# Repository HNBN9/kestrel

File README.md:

# Kestrel

Kestrel is a wireless Bluetooth split keyboard with a distinctive layout: a 3×5 − 2 main layout on both the left and right halves, each with two vertically arranged thumb keys.

The right half has a 19 mm trackball using the PMW3610 sensor, and the left half mirrors it with a 5-way switch. In total the keyboard has 32 + 5 keys (the 5 being the inputs of the 5-way switch).

It is designed with portability and usability in mind.

> > **Warning — Right Half Power Management**
>
> The current revision has a critical flaw in the right-side power management circuit. The LiPo charging and power delivery circuitry may not function correctly, potentially resulting in battery over-discharge and permanent damage.
>
> **If you still wish to use this revision**, remove all components belonging to the right-side boost converter circuit before connecting the LiPo battery directly to the XIAO's BAT+ and GND pads. Ensure that the battery charging and protection circuitry remains properly connected and functional.
>
> This workaround is provided as-is and has not been validated as a reliable fix. Use at your own risk.
>
> A redesigned power management circuit is planned for V2.

## Features

- Wireless Bluetooth split keyboard running ZMK
- 3×5 − 2 main layout with two vertical thumb keys per half
- 19 mm trackball (PMW3610) on the right half
- 5-way switch on the left half
- 3D-printed integrated hinge that bends close to 90° and provides built-in tenting
- Charlieplex matrix on the right half, with a dedicated 3V3 DC/DC converter circuit

## Specifications

| Item | Description |
|---|---|
| Form Factor | Split, wireless (Bluetooth) |
| Main Layout | 3×5 − 2, plus 2 vertical thumb keys per half |
| Keys | 32 + 5 (5-way switch) |
| Right Half | 19 mm trackball (PMW3610), charlieplex matrix, 3V3 DC/DC converter, central |
| Left Half | 5-way switch, standard key matrix, peripheral |
| Firmware | ZMK |
| Case | 3D-printed with integrated hinge |

## Hardware

### Hinge

The most distinctive feature of Kestrel is its 3D-printed hinge.

The built-in hinge bends close to 90° and supports tenting on its own. It keeps a suitable amount of torque for use on a keyboard.

### Left Half: 5-Way Switch

The left half uses a regular key matrix so that the 5-way switch can be included.

The 5-way switch supports a center click and pushing in four directions. However, it is prone to accidental inputs and its lifespan is not expected to be long. For this reason it is used for conservative functions such as arrow keys and switching between QWERTY and Colemak layers.

### Right Half: Trackball and Charlieplex Matrix

The right half uses a charlieplex matrix to work around the limited number of pins caused by the trackball. Because the trackball is on the right, the right half acts as the central and the left half as the peripheral.

Unlike col2row (or row2col) matrices, charlieplex pins have no fixed input and output roles, which makes it prone to ghosting. Charlieplex keyboards commonly deal with this by using the voltage drop across different numbers of diodes, so that a ghosted key falls outside the input range of the pin.

For this to work reliably, the supply voltage must stay constant. The right half therefore includes an additional 3V3 DC/DC converter circuit. Without it, ghosting increases sharply as the battery level drops.

> [!NOTE]
> The BOM for this design uses a WSON package for the 3V3 converter. If you do not order a PCBA, you will need to hand-solder the WSON package yourself. Modifying the circuit to use a similar-performance package that is easier to hand-solder is recommended.

### PCB

### Credits

- The charlieplex matrix is based on [Hooky's round-robin schematics](https://github.com/HookyKB/round-robin-schematics).
- The 3V3 circuit is based on [DYA Dash](https://github.com/cormoran/dya-dash-keyboard).
- The PMW3610 breakout board is a modified version of [ufan's pmw3610_breakout](https://github.com/ufan/pmw3610_breakout).

## Firmware

Kestrel runs on [ZMK Firmware](https://zmk.dev/).

The keyboard-specific configuration is maintained in a separate repository:

**[Kestrel ZMK Configuration](https://github.com/HNBN9/zmk-config-kestrel)**

The firmware files show how different matrices are applied to each half in ZMK. The matrix transform is shared between both halves, while the `kscan` configuration is written separately for the left and right halves.

## Gallery

## Known Issues

- The reverse-current blocking MOSFET in the right half's charging circuit has been reported to prevent proper charging. Remove the MOSFET and short its pads as a workaround (this removes the reverse-current protection).

## Repository Status

This repository currently contains the case STEP files and PCB-related files.

## License

This project uses separate licenses for software and non-software materials.

| Material | License |
|---|---|
| Firmware configuration and source code | [MIT License](./LICENSE-MIT) |
| Hardware design files (PCB, case), documentation, photographs, and renders | [CC BY-NC 4.0](./LICENSE-CC-BY-NC) |

Parts derived from other projects (see [Credits](#credits)) remain subject to the terms of their original authors.

ZMK Firmware itself is distributed under its own license; see the [ZMK repository](https://github.com/zmkfirmware/zmk).

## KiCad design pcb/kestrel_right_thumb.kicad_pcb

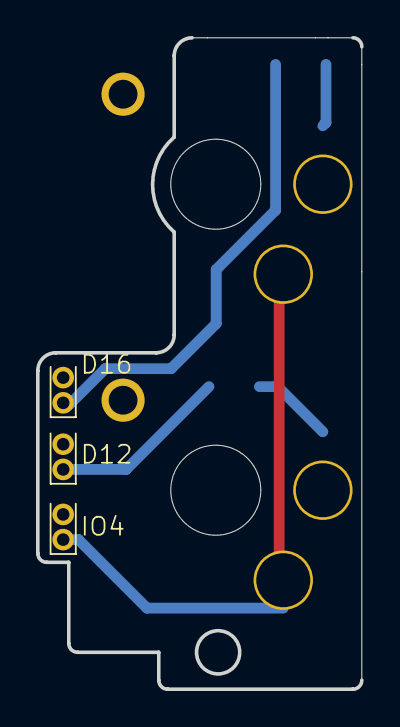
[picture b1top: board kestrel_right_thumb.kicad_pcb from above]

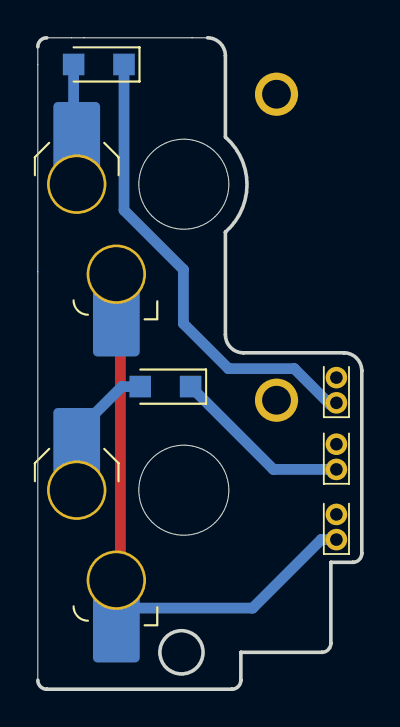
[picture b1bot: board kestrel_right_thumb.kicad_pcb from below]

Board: 2 copper layers, 18.0 x 36.2 mm, 4 parts (4 on the bottom side), 3 nets.

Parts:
D15, D16: 1N4148; Nexperia_CFP3_SOD-123W
RC4-3, RC4-4: SW_Push; SW_choc_v2_HS_CPG135001S30_1u

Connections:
IO 4: RC4-3.1, RC4-4.1
unnamed: D15.2 (A), RC4-3.2
unnamed: D16.2 (A), RC4-4.2

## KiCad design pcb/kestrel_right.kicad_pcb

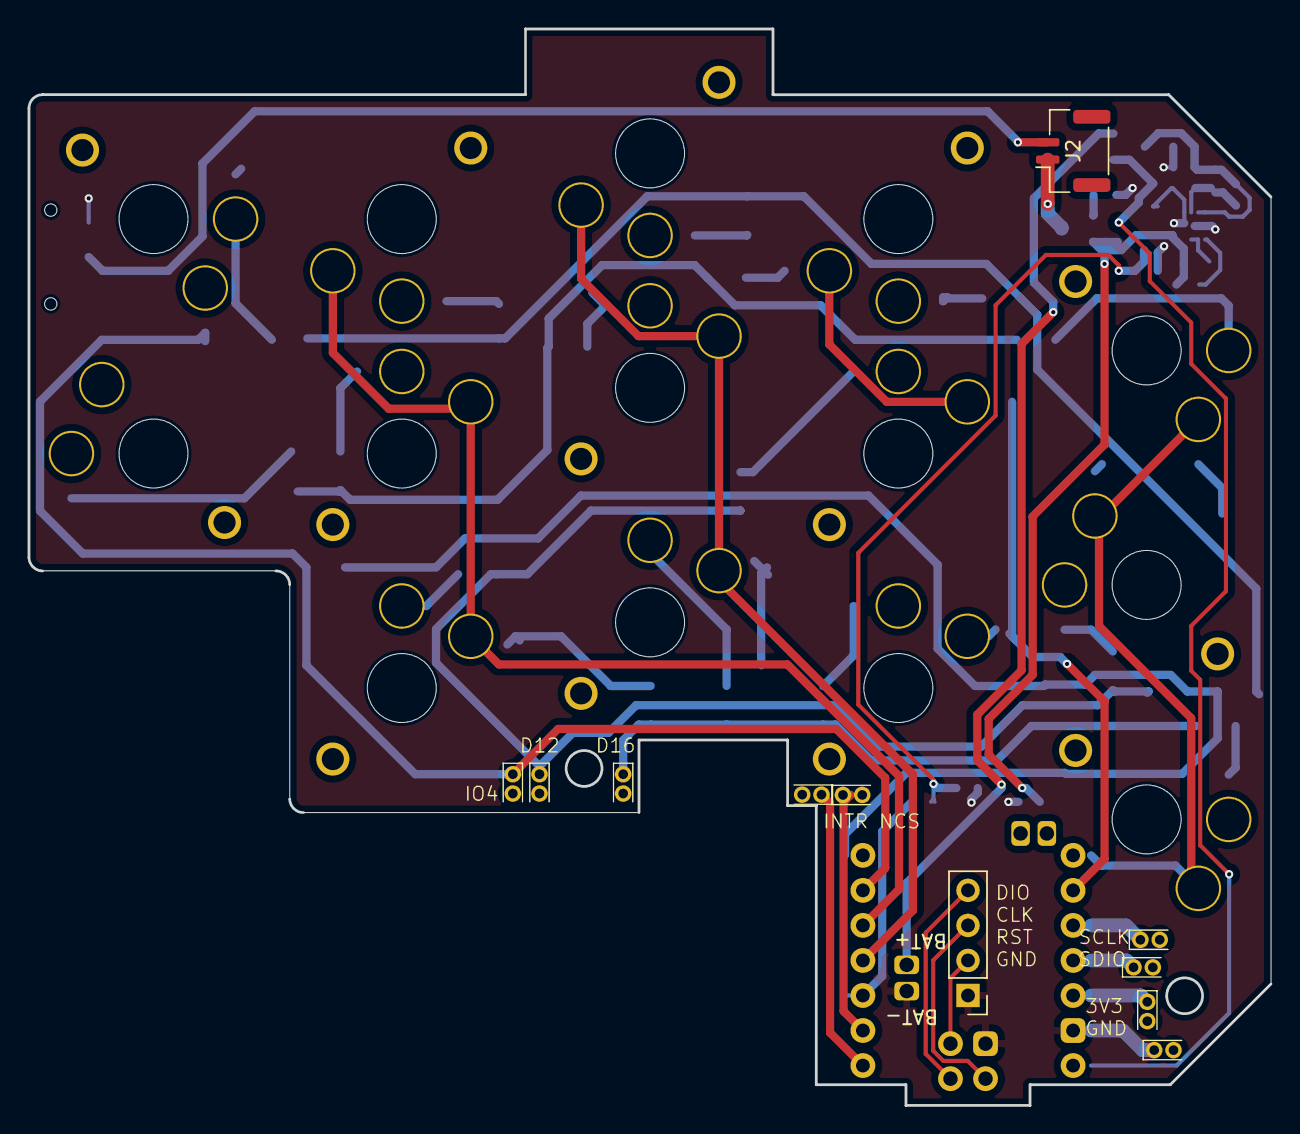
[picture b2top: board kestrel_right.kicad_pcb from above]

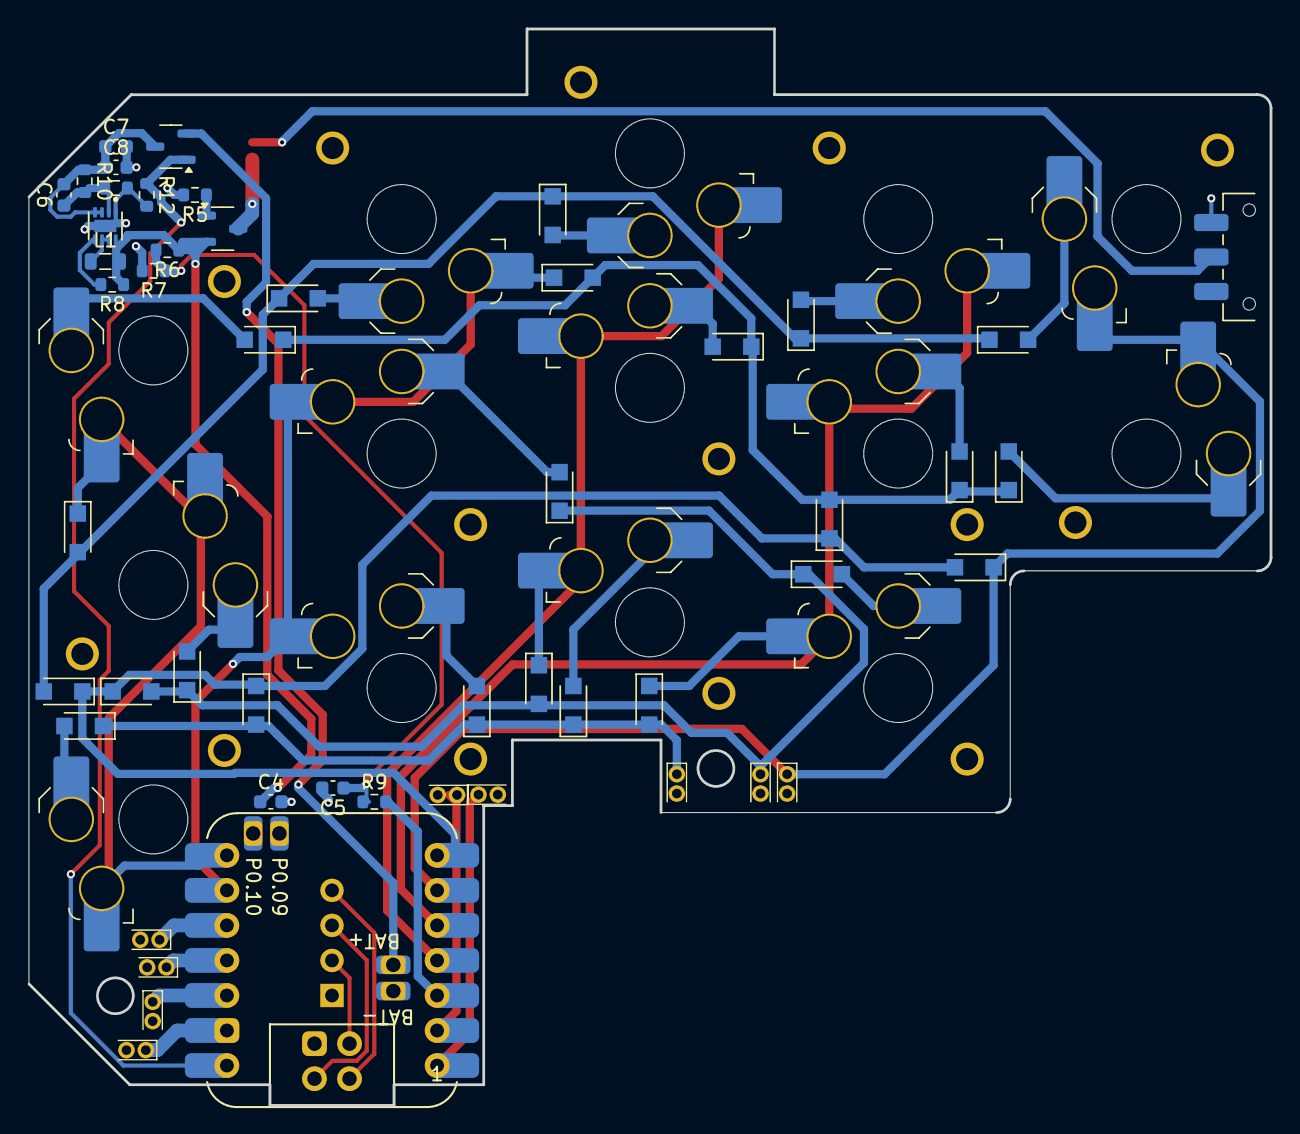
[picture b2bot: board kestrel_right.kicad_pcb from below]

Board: 2 copper layers, 90.0 x 78.0 mm, 57 parts (56 on the bottom side), 37 nets.

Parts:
C4: 10uF; C_0603_1608Metric
C5: 0.1uF; C_0603_1608Metric
C6: 20pf; C_0603_1608Metric
C7, C8: 10u; C_0603_1608Metric
D1, D2, D3, D4, D5, D6, D7, D8, D9, D10, D11, D12, D13, D14: 1N4148; Nexperia_CFP3_SOD-123W
DI1, DI2, DI3, DI4: 1N4148; Nexperia_CFP3_SOD-123W
DS1, DS2, DS3, DS4, DS5: 1N4148; Nexperia_CFP3_SOD-123W
J2: JST 1.25mm; JST_GH_SM02B-GHS-TB_1x02-1MP_P1.25mm_Horizontal
L1: 0.47uH; L_0805_2012Metric
Q2, Q3: AO3401A; SOT-23-3
R5, R8, R9, R12: 100k; R_0603_1608Metric
R6: 1M; R_0603_1608Metric
R7, R10: 470k; R_0603_1608Metric
R11: 150k; R_0603_1608Metric
RC0-1, RC0-2, RC0-3, RC1-1, RC1-2, RC1-3, RC2-1, RC2-2, RC2-3, RC3-1, RC3-2, RC3-3, RC4-1, RC4-2: SW_Push; SW_choc_v2_HS_CPG135001S30_1u
SW2: SW_SPDT; SW_SPDT_CK_JS102011SAQN
U2: TPS61021ADSGR
U3: Seeeduino Xiao nRF52840; Xiao_nRF52840_ACH

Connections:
BAT+: Q3.2 (S), U3.16 (BAT+)
GND: C4.2, C5.2, C7.2, C8.2, R5.2, R7.2, R11.2, R12.2, SW2.3 (C), U2.1 (AGND), U2.9 (PGND), U3.9 (GND), U3.15 (BAT-), U3.22 (GND)
INPUT_VOLTAGE: C5.1, R6.2, R7.1, R9.1
INTR: DI1.1 (K), DI2.1 (K), DI3.1 (K), DI4.1 (K), DS5.2 (A), U3.7 (P1.11)
IO 0: DS1.1 (K), RC0-1.1, RC0-2.1, RC0-3.1, U3.14 (P1.12)
IO 1: DS2.1 (K), RC1-1.1, RC1-2.1, RC1-3.1, U3.13 (P1.13)
IO 2: DS3.1 (K), RC2-1.1, RC2-2.1, RC2-3.1, U3.4 (P0.29)
IO 3: DS4.1 (K), RC3-1.1, RC3-2.1, RC3-3.1, U3.5 (P0.04)
IO 4: DS5.1 (K), RC4-1.1, RC4-2.1, U3.6 (P0.05)
unnamed: D1.2 (A), RC0-1.2
unnamed: D1.1 (K), D8.1 (K), D11.1 (K), D14.1 (K), DI2.2 (A), DS2.2 (A)
unnamed: D2.2 (A), RC0-2.2
unnamed: D3.2 (A), RC0-3.2
unnamed: D4.2 (A), RC1-1.2
unnamed: D5.2 (A), RC1-2.2
unnamed: D6.2 (A), RC1-3.2
unnamed: D7.2 (A), RC2-1.2
unnamed: D8.2 (A), RC2-2.2
unnamed: D9.2 (A), RC2-3.2
unnamed: D10.2 (A), RC3-1.2
unnamed: D4.1 (K), D7.1 (K), D10.1 (K), D13.1 (K), DI1.2 (A), DS1.2 (A)
unnamed: D11.2 (A), RC3-2.2
unnamed: D12.2 (A), RC3-3.2
unnamed: D2.1 (K), D5.1 (K), D12.1 (K), DI3.2 (A), DS3.2 (A)
unnamed: D13.2 (A), RC4-1.2
unnamed: D14.2 (A), RC4-2.2
unnamed: D3.1 (K), D6.1 (K), D9.1 (K), DI4.2 (A), DS4.2 (A)
unnamed: J2.1, Q2.3 (D)
unnamed: J2.2, SW2.2 (B)
unnamed: L1.1, U2.6 (SW), U2.7 (SW)
unnamed: Q2.1 (G), R5.1
unnamed: C4.1, L1.2, Q2.2 (S), R6.1, R8.1, U2.8 (VIN)
unnamed: C6.2, C7.1, C8.1, Q3.3 (D), R10.1, U2.3 (VOUT), U2.4 (VOUT)
unnamed: R8.2, U2.5 (EN)
unnamed: C6.1, R10.2, R11.1, U2.2 (FB)
unnamed: R9.2, U3.3 (P0.28)
VBUS: Q3.1 (G), R12.1, U3.8 (5V)

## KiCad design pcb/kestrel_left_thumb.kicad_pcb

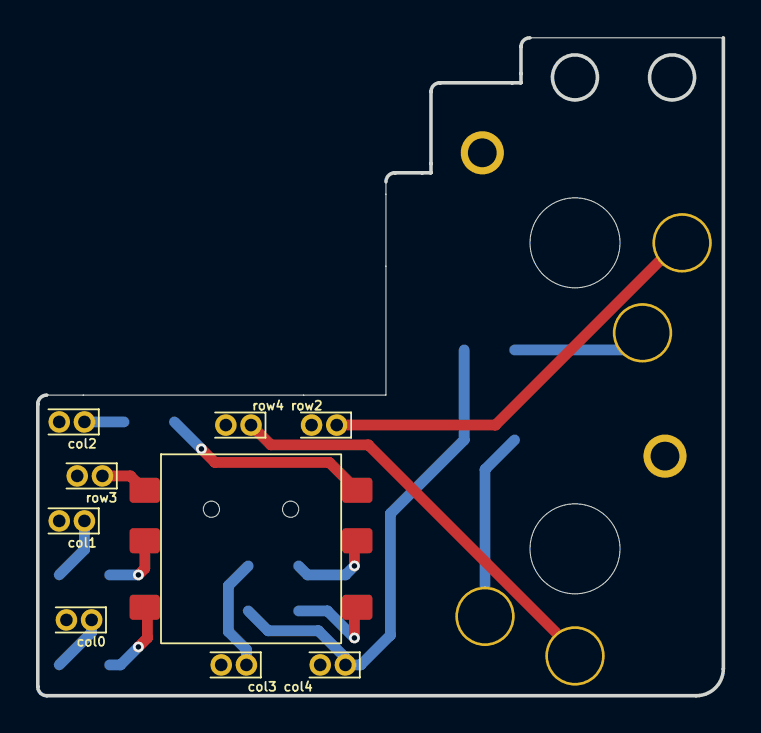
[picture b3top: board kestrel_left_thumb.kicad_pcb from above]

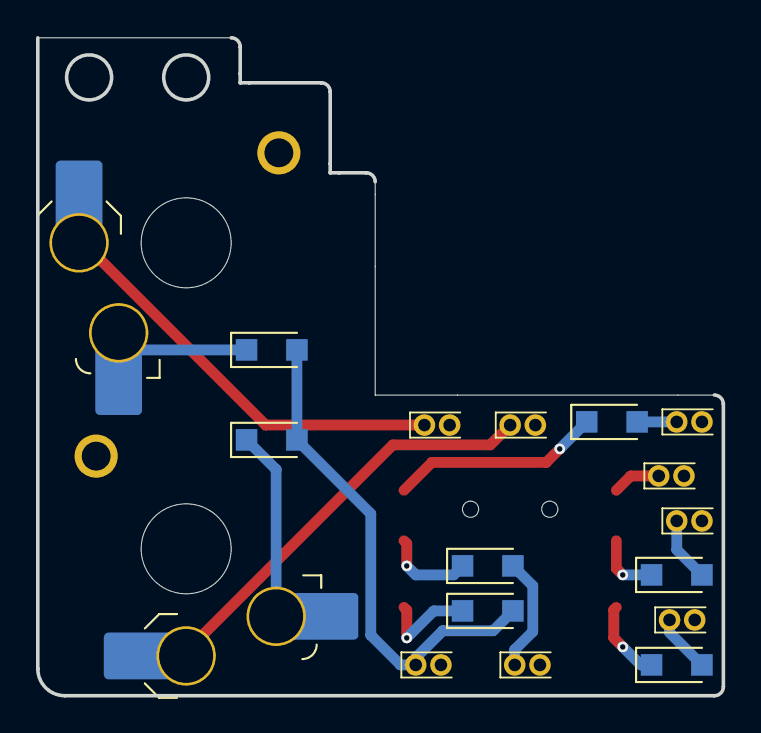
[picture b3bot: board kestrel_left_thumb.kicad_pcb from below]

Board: 2 copper layers, 38.1 x 36.5 mm, 10 parts (9 on the bottom side), 8 nets.

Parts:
5SW1: 5 way switch
DL1, DL5, DL9, DL13, DL17, DL20, DL21: 1N4148; Nexperia_CFP3_SOD-123W
LC15, LC16: SW_choc_v2_HS_CPG135001S30_1u

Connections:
unnamed: 5SW1.F2 (2), DL5.1 (K)
unnamed: 5SW1.F5 (3), DL1.1 (K)
unnamed: 5SW1.F1 (4), DL9.1 (K)
unnamed: 5SW1.F4 (5), DL13.1 (K)
unnamed: 5SW1.F3 (6), DL17.1 (K)
unnamed: DL20.1 (K), LC15.1
unnamed: DL21.1 (K), LC16.1
col4: DL17.2 (A), DL20.2 (A), DL21.2 (A)

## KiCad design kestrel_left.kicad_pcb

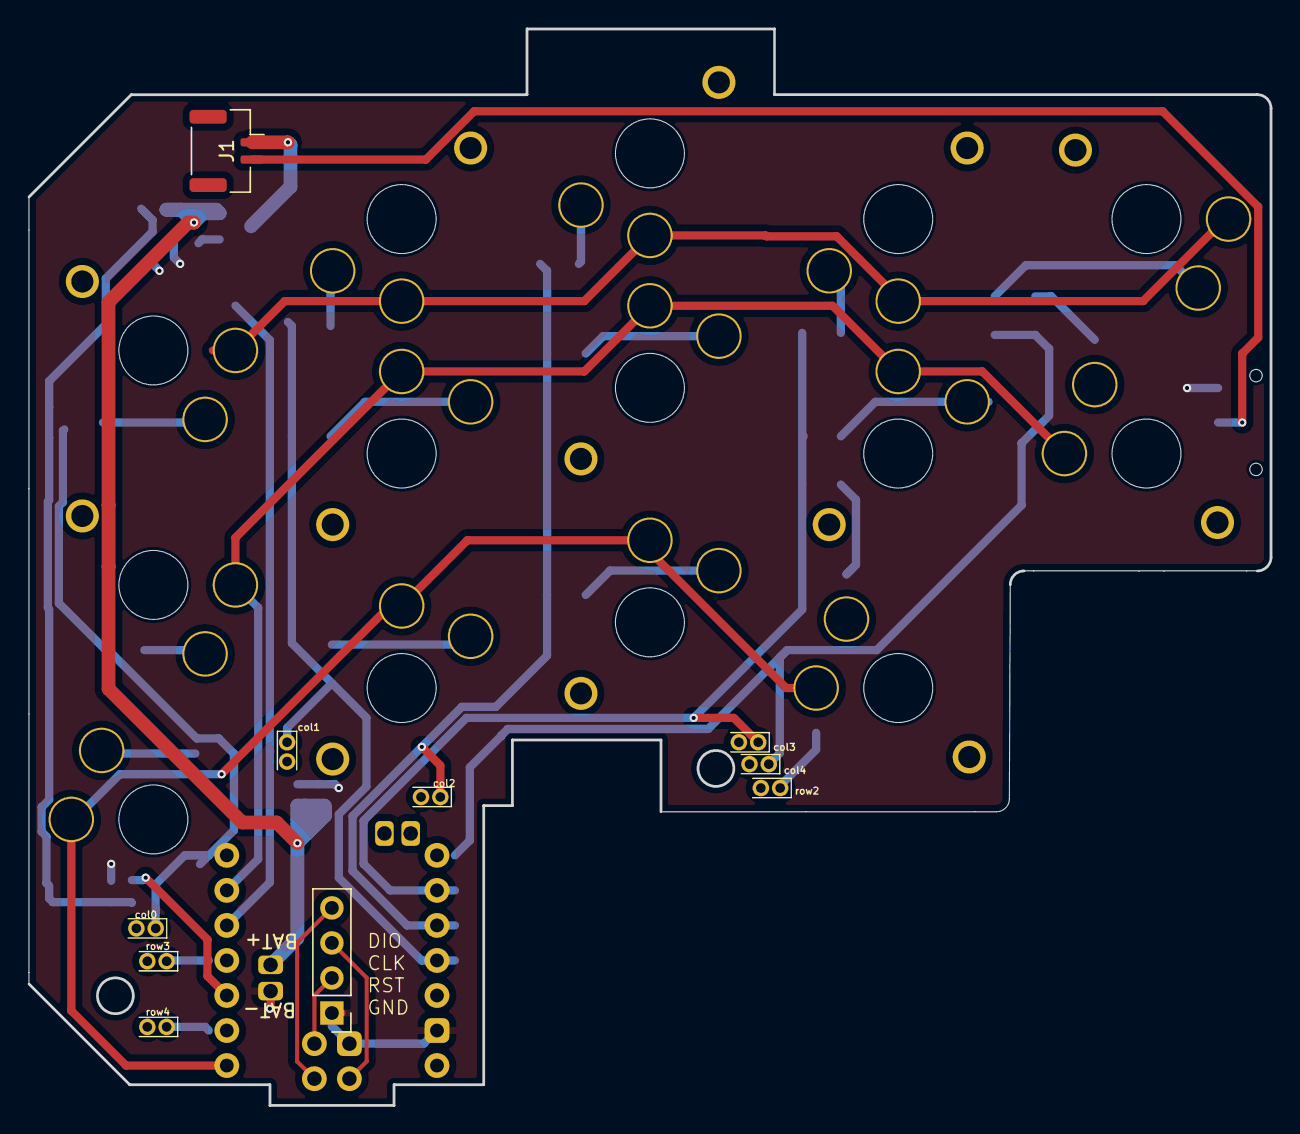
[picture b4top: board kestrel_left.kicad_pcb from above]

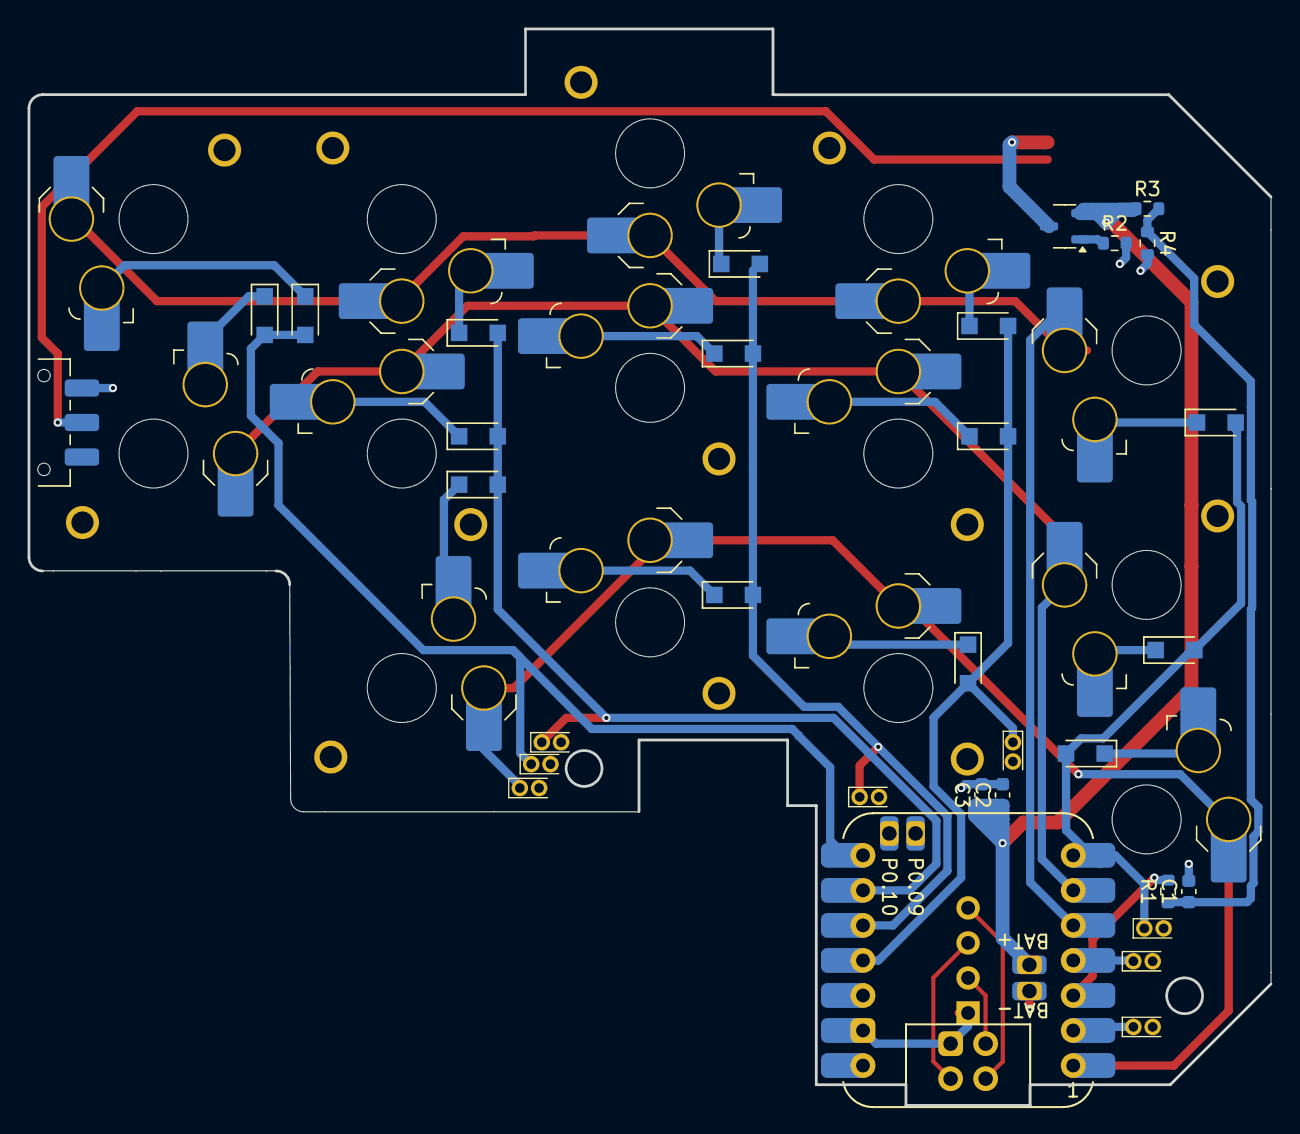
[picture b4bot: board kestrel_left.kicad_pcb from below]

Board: 2 copper layers, 90.1 x 78.0 mm, 39 parts (38 on the bottom side), 29 nets.

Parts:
C1, C3: 0.1uF; C_0603_1608Metric
C2: 10uF; C_0603_1608Metric
DL2, DL3, DL4, DL6, DL7, DL8, DL10, DL11, DL12, DL14, DL15, DL16, DL18, DL19: 1N4148; Nexperia_CFP3_SOD-123W
J1: JST 1.25mm; JST_GH_SM02B-GHS-TB_1x02-1MP_P1.25mm_Horizontal
LC1, LC2, LC3, LC4, LC5, LC6, LC7, LC8, LC9, LC10, LC11, LC12, LC13, LC14: SW_choc_v2_HS_CPG135001S30_1u
Q1: AO3401A; SOT-23-3
R1, R2: 100k; R_0603_1608Metric
R3: 1M; R_0603_1608Metric
R4: 470k; R_0603_1608Metric
SW1: SW_SPDT; SW_SPDT_CK_JS102011SAQN
U1: Seeeduino Xiao nRF52840; Xiao_nRF52840_ACH

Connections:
BAT+_L: C2.1, C3.1, Q1.2 (S), R3.1, U1.16 (BAT+)
GND_L: C1.2, C2.2, C3.2, R2.2, R4.2, SW1.1 (A), U1.9 (GND), U1.15 (BAT-), U1.22 (GND)
INPUT_VOLTAGE_L: C1.1, R1.1, R3.2, R4.1
unnamed: DL2.1 (K), LC1.1
unnamed: DL3.1 (K), LC2.1
unnamed: DL4.1 (K), LC3.1
unnamed: DL6.1 (K), LC4.1
unnamed: DL7.1 (K), LC5.1
unnamed: DL8.1 (K), LC6.1
unnamed: DL10.1 (K), LC7.1
unnamed: DL11.1 (K), LC8.1
unnamed: DL12.1 (K), LC9.1
unnamed: DL14.1 (K), LC10.1
unnamed: DL15.1 (K), LC11.1
unnamed: DL16.1 (K), LC12.1
unnamed: DL18.1 (K), LC13.1
unnamed: DL19.1 (K), LC14.1
unnamed: J1.1, Q1.3 (D)
unnamed: J1.2, SW1.2 (B)
unnamed: Q1.1 (G), R2.1
unnamed: R1.2, U1.3 (P0.28)
col0: DL2.2 (A), DL3.2 (A), DL4.2 (A), U1.7 (P1.11)
col1: DL6.2 (A), DL7.2 (A), DL8.2 (A), U1.11 (P1.15)
col2: DL10.2 (A), DL11.2 (A), DL12.2 (A), U1.12 (P1.14)
col3: DL14.2 (A), DL15.2 (A), DL16.2 (A), U1.13 (P1.13)
col4: DL18.2 (A), DL19.2 (A), U1.14 (P1.12)
row0: LC1.2, LC4.2, LC7.2, LC10.2, LC13.2, U1.5 (P0.04)
row1: LC2.2, LC5.2, LC8.2, LC11.2, LC14.2, U1.6 (P0.05)
row2: LC3.2, LC6.2, LC9.2, LC12.2, U1.1 (P0.02)

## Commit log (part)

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2026-01-26 Create pcb
2026-01-26 Rename kestrel_BOM.xlsx to pcb/kestrel_BOM.xlsx
